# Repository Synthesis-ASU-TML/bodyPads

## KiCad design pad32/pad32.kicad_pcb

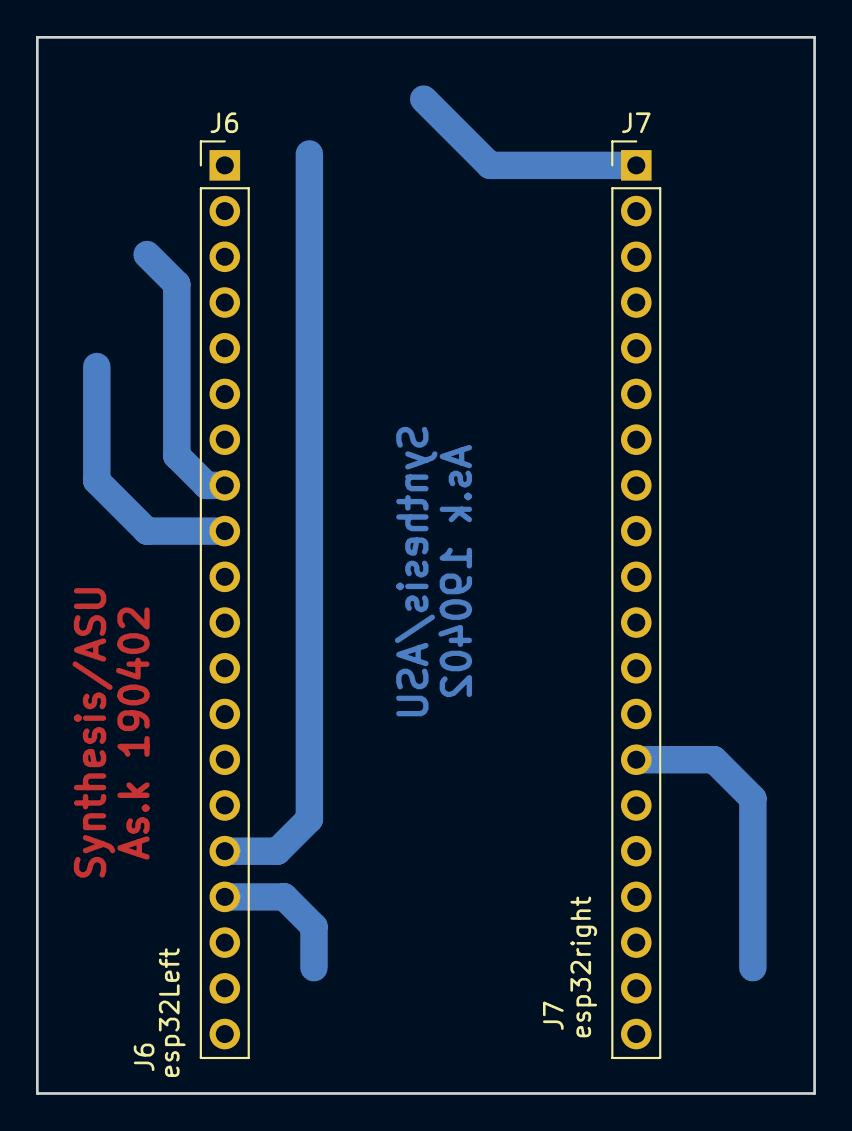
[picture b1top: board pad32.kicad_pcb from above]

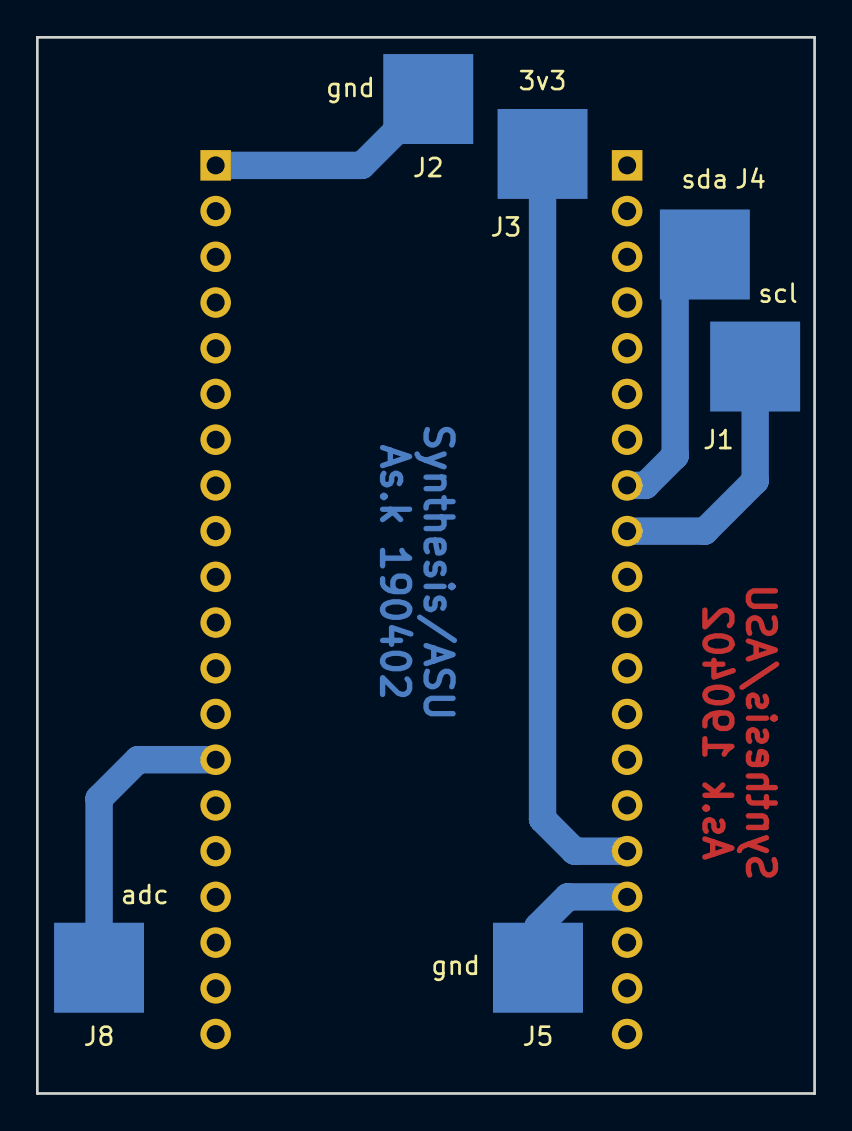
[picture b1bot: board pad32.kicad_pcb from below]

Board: 2 copper layers, 43.2 x 58.7 mm, 8 parts (6 on the bottom side), 6 nets.

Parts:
J1: scl; SolderWirePad_single_SMD_5x5mm
J2, J5: gnd; SolderWirePad_single_SMD_5x5mm
J3: 3v3; SolderWirePad_single_SMD_5x5mm
J4: sda; SolderWirePad_single_SMD_5x5mm
J6: esp32Left; Pin_Header_Straight_1x20_Pitch2.54mm
J7: esp32right; Pin_Header_Straight_1x20_Pitch2.54mm
J8: adc; SolderWirePad_single_SMD_5x5mm

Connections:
unnamed: J1.1, J6.9
unnamed: J2.1, J7.1
unnamed: J3.1, J6.16
unnamed: J4.1, J6.8
unnamed: J5.1, J6.17
unnamed: J7.14, J8.1
